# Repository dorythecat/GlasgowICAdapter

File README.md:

# GlasgowICAdapter
I wanted an adapter board to be able to use my ICs with my Glasgow Interface Explorer, without having to manually connect the leads one by one.

# On the design
The design, by default, uses four [TMUX1209](https://www.ti.com/lit/ds/symlink/tmux1208.pdf) Dual-Channel Multiplexers, which allows the Glasgow to communicate with ICs with up to 32 pins, whilst retaining a high speed, and still have four IOs left for general use. But, the objective of this board is to be *flexible*. And some chips don't just need digital IO, some need analog inputs and/or outputs, and some others even need higher speeds, if with less pins. For these reasons, you can disable each one of the four multiplexers individually with the EN_Ux bridges. When these pins are bridged, the appropiate multiplexer's outputs will be disabled, and you can use the breakout besides each of the two ports, in combination with the ZIF socket breakout, and some jumper cables, in order to properly connect everything as you need it.

# On the multiplexers
The multiplexers are wired 2-on-2 to each port. Four pins serve as the signal IOs (2,3,4,5), whilst two other pins (0,1), serve as the address selectors, which are wired so that both multiplexers on each channel share these address pins. The enable pins of the multiplexers are pulled up by one 10kOhm resistor each, and can be grounded by using its respective EN_Ux jumper. These multiplexe2rs support 1.8V logic, and are wired directly into the VIO of their respective port. This allows them to work with the full voltage range of the Glasgow.

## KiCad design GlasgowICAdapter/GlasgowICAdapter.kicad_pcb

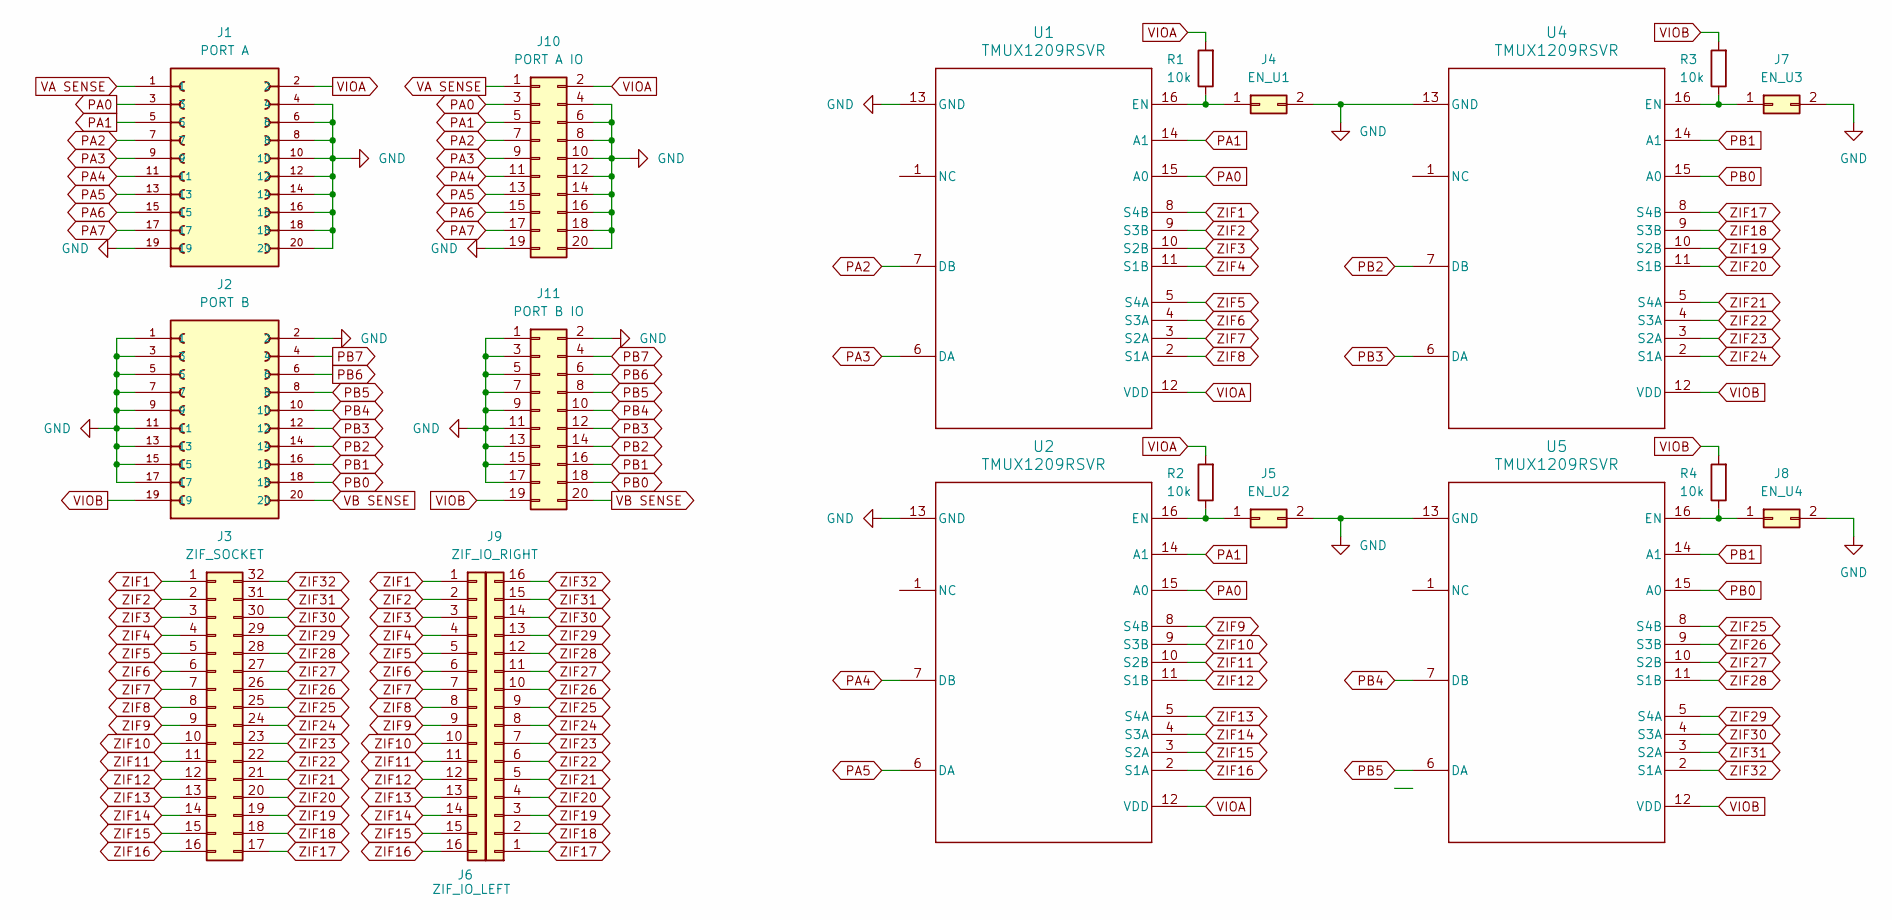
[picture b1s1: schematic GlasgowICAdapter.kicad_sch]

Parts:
J1: PORT A; CONN_SFH11-PBPC-D10-ST-BK_SUL; PARTREV J
J2: PORT B; CONN_SFH11-PBPC-D10-ST-BK_SUL; PARTREV J
J3: ZIF_SOCKET; DIP_Socket-32_W11.9mm_W12.7mm_W15.24mm_W17.78mm_W18.5mm_3M_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
J4: EN_U1; PinHeader_1x02_P2.54mm_Vertical
J5: EN_U2; PinHeader_1x02_P2.54mm_Vertical
J6: ZIF_IO_LEFT; PinHeader_1x16_P2.54mm_Vertical
J7: EN_U3; PinHeader_1x02_P2.54mm_Vertical
J8: EN_U4; PinHeader_1x02_P2.54mm_Vertical
J9: ZIF_IO_RIGHT; PinHeader_1x16_P2.54mm_Vertical
J10: PORT A IO; PinHeader_2x10_P2.54mm_Vertical
J11: PORT B IO; PinHeader_2x10_P2.54mm_Vertical
R1, R2, R3, R4: 10k; R_Axial_DIN0204_L3.6mm_D1.6mm_P7.62mm_Horizontal
U1, U2, U4, U5: TMUX1209RSVR; RSV0016A

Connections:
GND: J1.4, J1.6, J1.8, J1.10, J1.12, J1.14, J1.16, J1.18, J1.19, J1.20, J2.1, J2.2, J2.3, J2.5, J2.7, J2.9, J2.11, J2.13, J2.15, J2.17, J4.2, J5.2, J7.2, J8.2, J10.4, J10.6, J10.8, J10.10, J10.12, J10.14, J10.16, J10.18, J10.19, J10.20, J11.1, J11.2, J11.3, J11.5, J11.7, J11.9, J11.11, J11.13, J11.15, J11.17, U1.13 (GND), U2.13 (GND), U4.13 (GND), U5.13 (GND)
unnamed: J4.1, R1.1, U1.16 (EN)
unnamed: J5.1, R2.1, U2.16 (EN)
unnamed: J7.1, R3.1, U4.16 (EN)
unnamed: J8.1, R4.1, U5.16 (EN)
PA0: J1.3, J10.3, U1.15 (A0), U2.15 (A0)
PA1: J1.5, J10.5, U1.14 (A1), U2.14 (A1)
PA2: J1.7, J10.7, U1.7 (DB)
PA3: J1.9, J10.9, U1.6 (DA)
PA4: J1.11, J10.11, U2.7 (DB)
PA5: J1.13, J10.13, U2.6 (DA)
PA6: J1.15, J10.15
PA7: J1.17, J10.17
PB0: J2.18, J11.18, U4.15 (A0), U5.15 (A0)
PB1: J2.16, J11.16, U4.14 (A1), U5.14 (A1)
PB2: J2.14, J11.14, U4.7 (DB)
PB3: J2.12, J11.12, U4.6 (DA)
PB4: J2.10, J11.10, U5.7 (DB)
PB5: J2.8, J11.8, U5.6 (DA)
PB6: J2.6, J11.6
PB7: J2.4, J11.4
VA SENSE: J1.1, J10.1
VB SENSE: J2.20, J11.20
VIOA: J1.2, J10.2, R1.2, R2.2, U1.12 (VDD), U2.12 (VDD)
VIOB: J2.19, J11.19, R3.2, R4.2, U4.12 (VDD), U5.12 (VDD)
ZIF1: J3.1, J6.1, U1.8 (S4B)
ZIF2: J3.2, J6.2, U1.9 (S3B)
ZIF3: J3.3, J6.3, U1.10 (S2B)
ZIF4: J3.4, J6.4, U1.11 (S1B)
ZIF5: J3.5, J6.5, U1.5 (S4A)
ZIF6: J3.6, J6.6, U1.4 (S3A)
ZIF7: J3.7, J6.7, U1.3 (S2A)
ZIF8: J3.8, J6.8, U1.2 (S1A)
ZIF9: J3.9, J6.9, U2.8 (S4B)
ZIF10: J3.10, J6.10, U2.9 (S3B)
ZIF11: J3.11, J6.11, U2.10 (S2B)
ZIF12: J3.12, J6.12, U2.11 (S1B)
ZIF13: J3.13, J6.13, U2.5 (S4A)
ZIF14: J3.14, J6.14, U2.4 (S3A)
ZIF15: J3.15, J6.15, U2.3 (S2A)
ZIF16: J3.16, J6.16, U2.2 (S1A)
ZIF17: J3.17, J9.1, U4.8 (S4B)
ZIF18: J3.18, J9.2, U4.9 (S3B)
ZIF19: J3.19, J9.3, U4.10 (S2B)
ZIF20: J3.20, J9.4, U4.11 (S1B)
ZIF21: J3.21, J9.5, U4.5 (S4A)
ZIF22: J3.22, J9.6, U4.4 (S3A)
ZIF23: J3.23, J9.7, U4.3 (S2A)
ZIF24: J3.24, J9.8, U4.2 (S1A)
ZIF25: J3.25, J9.9, U5.8 (S4B)
ZIF26: J3.26, J9.10, U5.9 (S3B)
ZIF27: J3.27, J9.11, U5.10 (S2B)
ZIF28: J3.28, J9.12, U5.11 (S1B)
ZIF29: J3.29, J9.13, U5.5 (S4A)
ZIF30: J3.30, J9.14, U5.4 (S3A)
ZIF31: J3.31, J9.15, U5.3 (S2A)
ZIF32: J3.32, J9.16, U5.2 (S1A)

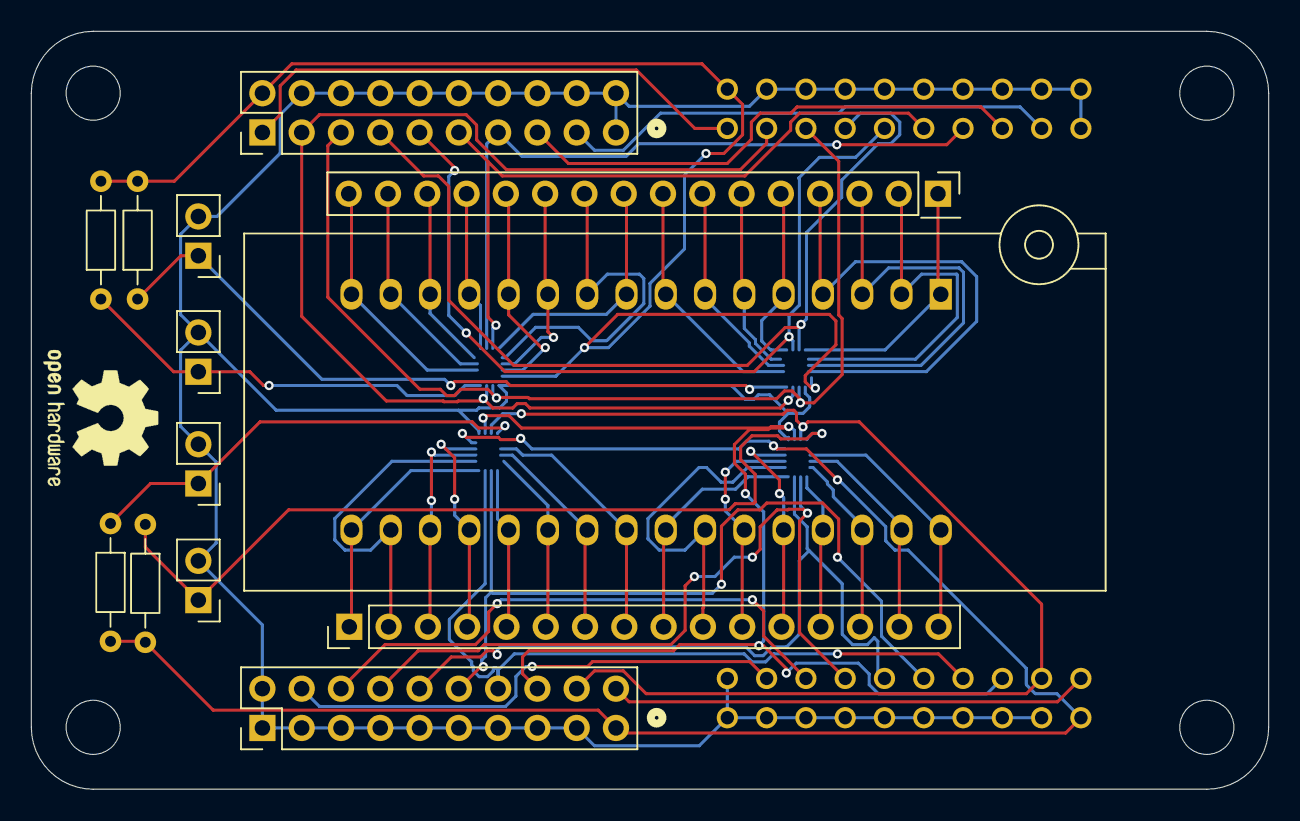
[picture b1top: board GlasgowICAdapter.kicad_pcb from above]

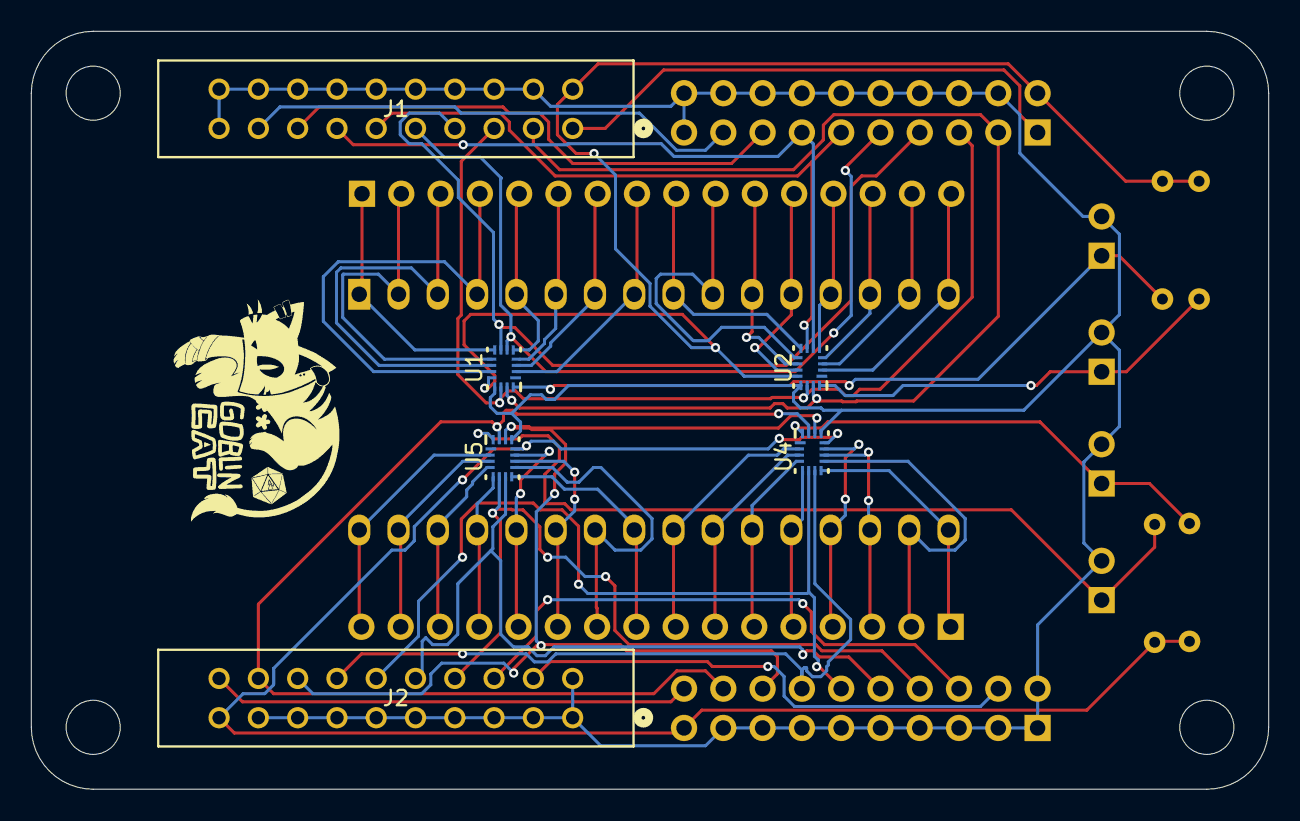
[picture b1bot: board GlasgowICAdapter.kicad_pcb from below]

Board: 2 copper layers, 80.0 x 49.0 mm, 19 parts (6 on the bottom side), 57 nets.

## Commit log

2025-10-13 Added A and B ports and populated labels properly
2025-10-15 Added ZIF socket and chips, routed basics
2025-10-15 Added IO ports for both ports and for ZIF socket
2025-10-15 Finally connected everything together
2025-10-15 Added schematic PDF
2025-10-20 Added proper footprints to all symbols
2025-10-20 Layed out all the footprints in the PCB
2025-10-20 Added PCB holes
2025-10-20 Slightly imporved schematic
2025-10-20 Finished PCB routing, finally :D
2025-10-21 Fixed PCB a little bit
2025-10-21 Added silkscreens
2025-10-21 Plotted gerber files
2025-10-21 Added 3D model of board
2025-10-21 Added raytraced render of the board
2025-10-21 Add raytraced render image to README
    Added a raytraced render image of the board to the README.
2025-10-21 Added bom.csv
